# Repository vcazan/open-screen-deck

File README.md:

# Open Screen Deck

Six Waveshare ScreenKey modules (128×128 IPS + switch in each cap) on an
ESP32-S3 carrier you have fabricated, in a case you print. This repo is
the KiCad, Gerbers, OpenSCAD, STLs, firmware, and an optional desktop
companion.

[Build notes](https://vcazan.github.io/open-screen-deck/) ·
[Latest release](https://github.com/vcazan/open-screen-deck/releases/latest)
(macOS/Windows app + firmware `.bin`) ·
[Discord](https://discord.gg/PVCzBBeGQX)

## Build one

1. **Order** — 6× [Waveshare 34168](https://www.waveshare.com/0.85inch-screenkey.htm?sku=34168)
   (about $66, longest lead time). Upload
   [`hardware/pcb/data_streamdeck_gerbers.zip`](hardware/pcb/data_streamdeck_gerbers.zip)
   to [JLCPCB](https://jlcpcb.com) (about $15 for five boards). Full list:
   [`hardware/bom_assembly.csv`](hardware/bom_assembly.csv)
2. **Print** while those ship — four STLs in [`hardware/enclosure/stl/`](hardware/enclosure/stl/),
   PETG or PLA+, no supports:
   `deck_bottom_v14.stl`, `deck_top_v14.stl`, `corner_spacers_x4_v14.stl`,
   optional `deck_stand_v14.stl`
3. **Assemble** — [guide](https://vcazan.github.io/open-screen-deck/build/assembly/),
   about 45 minutes
4. **Flash** over USB-C — [companion](https://github.com/vcazan/open-screen-deck/releases/latest)
   (Settings → Firmware) or Arduino /
   [esptool](https://vcazan.github.io/open-screen-deck/firmware/flashing/).
   Same release has `firmware-0.14.5.bin` plus bootloader and partitions.

Parts land around **$100**. The six modules are most of that. v14 STLs
match the **Rev E** board (59.5 × 108.5 mm); don’t mix with older v13 prints.

| | |
|--|--|
| **Keys** | 6× Waveshare 0.85″ ScreenKey (SKU 34168) |
| **Board** | ESP32-S3-WROOM-1-N16R8 on a **59.5 × 108.5 mm** Rev E carrier |
| **On board** | IMU, VEML7700 ALS, DRV2605L haptics, piezo, 8× SK6812, Qwiic |
| **Displays** | Dual SPI (J1–J3 + SD / J4–J6), 40 MHz + DMA |
| **Case** | 64.9 × 113.9 × 28.2 mm printed deck + optional 25° stand |
| **Firmware** | 0.14.5 (protocol 14) — HID keyboard F13–F24 by default |

Pinout lives in [`hardware/pinout.py`](hardware/pinout.py). Generators
refuse to run if `firmware/config.h` disagrees.

## Firmware

Sources in [`firmware/`](firmware/). Out of the box it types F13–F24.
Pages, labels, icons, microSD animations, auto-dim, glow LEDs, and haptics
are configured over USB serial
([protocol](https://vcazan.github.io/open-screen-deck/firmware/protocol/)).

Prebuilt images are on
[Releases](https://github.com/vcazan/open-screen-deck/releases/latest)
(`firmware-0.14.5.bin`, `.bootloader.bin`, `.partitions.bin`). The companion
bundles the same files. To compile locally:

```bash
./scripts/build_firmware.sh          # also copies bins into the app
./scripts/build_firmware.sh --flash  # then upload to a connected deck
```

Arduino: ESP32S3 Dev Module, USB CDC On Boot enabled, USB-OTG, OPI PSRAM,
16 MB flash (`app3M_fat9M_16MB`). Libraries: Adafruit GFX, ST7735, NeoPixel.

## Companion app

Optional. The deck is a USB keyboard without it. Use the app to draw key
faces, bind host actions, flash firmware, and (on Rev E) drive auto-dim /
glow / self-test.

- **Download:** [Releases](https://github.com/vcazan/open-screen-deck/releases/latest)
  — macOS `.dmg` (unsigned: right-click → Open), Windows `.msi`
- **From source:** `cd app && npm install && npx tauri dev`
- **Plugins:** folders in [`plugins/`](plugins/);
  [directory](https://vcazan.github.io/open-screen-deck/plugins/) ·
  [`plugins/registry.json`](plugins/registry.json)

A push to `main` updates this repo and the docs site. A **GitHub Release**
(installers + firmware bins) is created only when a tag `app-v*` is pushed,
e.g. `app-v0.2.0`.

## Repo map

```
hardware/
  pinout.py          Canonical GPIO + Rev E geometry
  pcb/               KiCad, Gerbers, board BOM
  enclosure/         OpenSCAD v14 + printable STLs
  3d/                Fastener / assembly STEP
firmware/            ESP32-S3 Arduino (0.14.5)
app/                 Tauri companion (Rust + React)
plugins/             Bundled plugins + registry.json
profiles/            Shared layouts (.osdprofile.json)
docs/                MkDocs site
scripts/             PCB / schematic / firmware helpers
```

## Contributing

- **Plugins** — folder in `plugins/` + a registry line
  ([how](https://vcazan.github.io/open-screen-deck/plugins/develop/))
- **Profiles** — export from the app, PR into `profiles/`
- **Hardware** — OpenSCAD is parametric; keep the
  [mechanical contract](docs/mechanical_contract.md) if the PCB should still fit
- **App / firmware** — `cd app && npm test && npm run test:e2e`

## Related projects

Same neighbourhood: [FreeTouchDeck](https://github.com/DustinWatts/FreeTouchDeck)
(one touchscreen), [open-deck](https://github.com/joshr120/open-deck) (one TFT
behind keys), [MacroPad](https://github.com/yuvasaro/MacroPad) (per-key OLED).
This one is six discrete ScreenKey modules on a carrier you can order.

## License

- **Firmware, app, scripts, docs:** [MIT](LICENSE)
- **Hardware (PCB + enclosure):** [CERN-OHL-P v2](hardware/LICENSE)

ScreenKey modules are a [Waveshare](https://www.waveshare.com) product; this
project is not affiliated with or endorsed by Waveshare or Elgato.

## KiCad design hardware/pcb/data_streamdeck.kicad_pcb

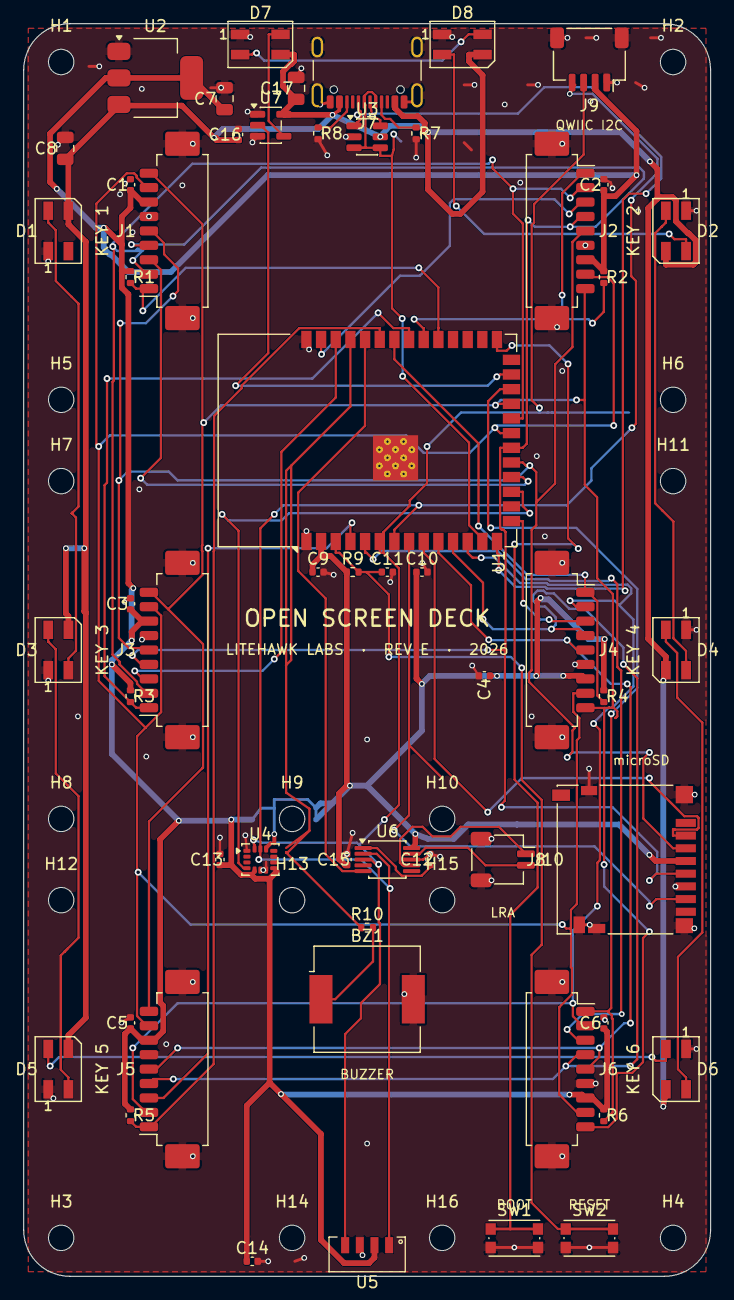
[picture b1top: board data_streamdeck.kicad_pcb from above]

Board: 2 copper layers, 59.5 x 108.5 mm, 71 parts (0 on the bottom side), 49 nets.

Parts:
BZ1: CPT-9019S; Buzzer_CUI_CPT-9019S-SMT
C1, C2, C3, C4, C5, C6, C9, C10, C13, C14, C15, C16: 100nF; C_0402_1005Metric
C7, C8, C17: 10uF; C_0805_2012Metric
C11, C12: 1uF; C_0402_1005Metric
D1, D2, D3, D4, D5, D6, D7, D8: SK6812MINI-E; LED_SK6812MINI_PLCC4_3.5x3.5mm_P1.75mm
H1, H2, H3, H4: M2-corner-case-screw; MountingHole_2.2mm_M2
H5, H6, H7, H8, H9, H10, H11, H12, H13, H14, H15, H16: M2-module-standoff; MountingHole_2.2mm_M2
J1: ScreenKey 1; Molex_PicoBlade_53261-0971_1x09-1MP_P1.25mm_Horizontal
J2: ScreenKey 2; Molex_PicoBlade_53261-0971_1x09-1MP_P1.25mm_Horizontal
J3: ScreenKey 3; Molex_PicoBlade_53261-0971_1x09-1MP_P1.25mm_Horizontal
J4: ScreenKey 4; Molex_PicoBlade_53261-0971_1x09-1MP_P1.25mm_Horizontal
J5: ScreenKey 5; Molex_PicoBlade_53261-0971_1x09-1MP_P1.25mm_Horizontal
J6: ScreenKey 6; Molex_PicoBlade_53261-0971_1x09-1MP_P1.25mm_Horizontal
J7: USB4105-GF-A; USB_C_Receptacle_GCT_USB4105-xx-A_16P_TopMnt_Horizontal
J8: microSD; microSD_HC_Hirose_DM3D-SF
J9: Qwiic; JST_SH_SM04B-SRSS-TB_1x04-1MP_P1.00mm_Horizontal
J10: LRA motor; JST_SH_SM02B-SRSS-TB_1x02-1MP_P1.00mm_Horizontal
R1, R2, R3, R4, R5, R6, R9: 10k; R_0402_1005Metric
R7, R8: 5.1k; R_0402_1005Metric
R10: 100R; R_0402_1005Metric
SW1: BOOT; SW_Push_1P1T_NO_CK_KMR2
SW2: RESET; SW_Push_1P1T_NO_CK_KMR2
U1: ESP32-S3-WROOM-1-N16R8; ESP32-S3-WROOM-1
U2: AMS1117-3.3; SOT-223-3_TabPin2
U3: USBLC6-2SC6; SOT-23-6
U4: LSM6DS3TR-C; LGA-14_3x2.5mm_P0.5mm_LayoutBorder3x4y
U5: VEML7700; VEML7700-TT
U6: DRV2605L; MSOP-10_3x3mm_P0.5mm
U7: 74AHCT1G125; SOT-23-5

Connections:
+3V3: C1.1, C2.1, C3.1, C4.1, C5.1, C6.1, C7.1, C9.1, C10.1, C13.1, C14.1, C15.1, J1.7, J2.7, J3.7, J4.7, J5.7, J6.7, J8.4, J9.2, R1.1, R2.1, R3.1, R4.1, R5.1, R6.1, R9.1, U1.2, U2.2, U4.5, U4.8, U4.12, U5.2, U6.10
BL: J1.8, J2.8, J3.8, J4.8, J5.8, J6.8, U1.21
BOOT: SW1.1, U1.27
CC1: J7.A5, R7.1
CC2: J7.B5, R8.1
CS1: J1.3, U1.18
CS2: J2.3, U1.39
CS3: J3.3, U1.38
CS4: J4.3, U1.15
CS5: J5.3, U1.4
CS6: J6.3, U1.5
DC_A: J1.2, J2.2, J3.2, U1.22
DC_B: J4.2, J5.2, J6.2, U1.12
DRV_REG: C12.1, U6.1
EN: C11.1, R9.2, SW2.1, U1.3
GND: BZ1.2, C1.2, C2.2, C3.2, C4.2, C5.2, C6.2, C7.2, C8.2, C9.2, C10.2, C11.2, C12.2, C13.2, C14.2, C15.2, C16.2, C17.2, D1.1, D2.1, D3.1, D4.1, D5.1, D6.1, D7.1, D8.1, J1.6, J1.MP, J2.6, J2.MP, J3.6, J3.MP, J4.6, J4.MP, J5.6, J5.MP, J6.6, J6.MP, J7.A1, J7.A12, J7.B1, J7.B12, J7.SH, J8.6, J8.9, J8.SH, J9.1, J9.MP, J10.MP, R7.2, R8.2, SW1.2, SW2.2, U1.1, U1.40, U1.41, U2.1, U3.2, U4.1, U4.6, U4.7, U5.3, U6.8, U7.1, U7.3
HAPTIC_EN: U1.36, U6.5
HAP_N: J10.2, U6.9
HAP_P: J10.1, U6.7
IMU_INT: U1.17, U4.4
KEY1: J1.1, R1.2, U1.31
KEY2: J2.1, R2.2, U1.32
KEY3: J3.1, R3.2, U1.33
KEY4: J4.1, R4.2, U1.34
KEY5: J5.1, R5.2, U1.35
KEY6: J6.1, R6.2, U1.24
LED_CH1: D7.2, D8.4
LED_CH2: D2.4, D8.2
LED_CH3: D2.2, D4.4
LED_CH4: D4.2, D6.4
LED_CH5: D5.4, D6.2
LED_CH6: D3.4, D5.2
LED_CH7: D1.4, D3.2
LED_DATA_3V3: U1.25, U7.2
LED_DATA_5V: D7.4, U7.4
MISO: J8.7, U1.8
MOSI_A: J1.5, J2.5, J3.5, J8.3, U1.19
MOSI_B: J4.5, J5.5, J6.5, U1.10
PIEZO: R10.1, U1.37
PIEZO_BZ: BZ1.1, R10.2
RST: J1.9, J2.9, J3.9, J4.9, J5.9, J6.9, U1.23
SCK_A: J1.4, J2.4, J3.4, J8.5, U1.20
SCK_B: J4.4, J5.4, J6.4, U1.11
SCL: J9.4, U1.7, U4.13, U5.1, U6.2
SDA: J9.3, U1.6, U4.14, U5.4, U6.3
SD_CS: J8.2, U1.9
USB_D+: J7.A6, J7.B6, U1.14, U3.1, U3.6
USB_D-: J7.A7, J7.B7, U1.13, U3.3, U3.4
VBUS: C8.1, C16.1, C17.1, D1.3, D2.3, D3.3, D4.3, D5.3, D6.3, D7.3, D8.3, J7.A4, J7.A9, J7.B4, J7.B9, U2.3, U3.5, U7.5

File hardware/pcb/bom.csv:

Reference,Value,Footprint,Qty,MPN,Supplier,Notes
H1-H4,MountingHole 2.2mm,MountingHole:MountingHole_2.2mm_M2,4,,,M2x25 corner case screws pass through into the corner-module nuts
H5-H16,MountingHole 2.2mm,MountingHole:MountingHole_2.2mm_M2,12,,,Module standoff clearance holes (M2x5 into ScreenKey factory standoffs)
J1-J6,Molex PicoBlade 9P right-angle,Connector_Molex:Molex_PicoBlade_53261-0971_1x09-1MP_P1.25mm_Horizontal,6,53261-0971,Molex,Same MX1.25/PicoBlade family as the module connector; in-box cable plugs in; pin1=KEY. Verified alternate: HDGC HDGC1251WR-S-9P (SMT PicoBlade clone; JLC-stocked)
J7,USB-C receptacle,Connector_USB:USB_C_Receptacle_GCT_USB4105-xx-A_16P_TopMnt_Horizontal,1,USB4105-GF-A,GCT,Horizontal top-mount; port exits rear board edge @ X=29.75mm
J8,microSD push-push,Connector_Card:microSD_HC_Hirose_DM3D-SF,1,DM3D-SF,Hirose,Card ejects right board edge; SPI mode on bus A
J9,Qwiic / StemmaQT 4P,Connector_JST:JST_SH_SM04B-SRSS-TB_1x04-1MP_P1.00mm_Horizontal,1,SM04B-SRSS-TB,JST,I2C expansion; exits rear wall next to USB
J10,LRA motor 2P,Connector_JST:JST_SH_SM02B-SRSS-TB_1x02-1MP_P1.00mm_Horizontal,1,SM02B-SRSS-TB,JST,Haptic LRA (e.g. Vybronics VG0832013D) plugs in
U1,ESP32-S3-WROOM-1-N16R8,RF_Module:ESP32-S3-WROOM-1,1,ESP32-S3-WROOM-1-N16R8,Espressif,16MB flash 8MB PSRAM native USB; dual SPI display driver
U2,AMS1117-3.3,Package_TO_SOT_SMD:SOT-223-3_TabPin2,1,AMS1117-3.3,AMS,1A 3.3V LDO from USB 5V — headroom for 6 backlights + SD + sensors
U3,USBLC6-2SC6,Package_TO_SOT_SMD:SOT-23-6,1,USBLC6-2SC6,ST,USB ESD protection on D+/D-/VBUS
U4,LSM6DS3TR-C IMU,Package_LGA:LGA-14_3x2.5mm_P0.5mm_LayoutBorder3x4y,1,LSM6DS3TR-C,ST,6-axis accel+gyro; INT1 on IO9 for wake-on-pickup / tap
U5,VEML7700 ambient light,OpenScreenDeck:VEML7700-TT,1,VEML7700-TT,Vishay,I2C ALS for auto backlight dimming; needs light window in enclosure front
U6,DRV2605L haptic driver,Package_SO:MSOP-10_3x3mm_P0.5mm,1,DRV2605LDGSR,TI,LRA driver with effect library; EN on IO44
U7,74AHCT1G125 level shifter,Package_TO_SOT_SMD:SOT-23-5,1,SN74AHCT1G125DBVR,TI,3.3V -> 5V LED data buffer for SK6812 chain
D1-D8,SK6812MINI-E RGB LED,LED_SK6812MINI:LED_SK6812MINI_PLCC4_3.5x3.5mm_P1.75mm,8,SK6812MINI-E,OPSCO,Edge-glow chain: 2 rear + 6 side; 5V VBUS powered; data from U7
BZ1,Piezo buzzer,Buzzer_Beeper:Buzzer_CUI_CPT-9019S-SMT,1,CPT-9019S-SMT-TR,CUI,4kHz passive piezo; LEDC tone on IO43 via R10
SW1,BOOT tactile C&K KMR2,Button_Switch_SMD:SW_Push_1P1T_NO_CK_KMR2,1,KMR221GLFS,C&K,GPIO0 strap — hold for USB download mode
SW2,RESET tactile C&K KMR2,Button_Switch_SMD:SW_Push_1P1T_NO_CK_KMR2,1,KMR221GLFS,C&K,EN to GND — tap while holding BOOT to enter bootloader
C1-C6,100nF 0402,Capacitor_SMD:C_0402_1005Metric,6,,,Per ScreenKey VCC
C7,10uF 0805,Capacitor_SMD:C_0805_2012Metric,1,,,LDO output bulk
C8,10uF 0805,Capacitor_SMD:C_0805_2012Metric,1,,,LDO input
C9-C11,100nF/1uF 0402,Capacitor_SMD:C_0402_1005Metric,3,,,ESP32 decoupling + EN RC
C12,1uF 0402,Capacitor_SMD:C_0402_1005Metric,1,,,DRV2605L VREG
C13-C15,100nF 0402,Capacitor_SMD:C_0402_1005Metric,3,,,IMU / ALS / haptic decoupling
C16,100nF 0402,Capacitor_SMD:C_0402_1005Metric,1,,,Level shifter 5V decoupling
C17,10uF 0805,Capacitor_SMD:C_0805_2012Metric,1,,,LED 5V rail bulk
R1-R6,10k 0402,Resistor_SMD:R_0402_1005Metric,6,,,KEY line pull-ups
R7-R8,5.1k 0402,Resistor_SMD:R_0402_1005Metric,2,,,USB-C CC1/CC2 pulldowns
R9,10k 0402,Resistor_SMD:R_0402_1005Metric,1,,,EN pull-up
R10,100R 0402,Resistor_SMD:R_0402_1005Metric,1,,,Piezo series resistor

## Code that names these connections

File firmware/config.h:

/**
 * config.h — every pin, constant, and tunable in one place.
 *
 * The canonical pinout lives in hardware/pinout.py: the PCB/schematic
 * generators cross-check this file against it at generation time and
 * hard-fail on divergence. If you change a pin here, change pinout.py
 * and regenerate the hardware in the same commit.
 */

#pragma once

#include <Arduino.h>

// ── Identity ────────────────────────────────────────────────────────
#define FIRMWARE_VERSION "0.14.5"
#define PROTOCOL_VERSION 14

// ── Debug ───────────────────────────────────────────────────────────
// 1 → emit {"event":"dbg",...} lines for every draw/blit/batch change so
// the companion console shows exactly which slot hits which display.
#define DEBUG_DRAW 1

// ── Pins (ESP32-S3-WROOM-1 on the Rev E carrier PCB) ────────────────
// SPI bus A (FSPI): panels J1-J3 + microSD
#define PIN_MOSI_A 11
#define PIN_SCK_A  12
#define PIN_MISO   15   // SD read (displays are write-only)
#define PIN_DC_A   14
#define PIN_SD_CS  16   // microSD chip select
// SPI bus B (HSPI): panels J4-J6
#define PIN_MOSI_B 17
#define PIN_SCK_B  18
#define PIN_DC_B   8
// Shared display lines
#define PIN_RST 21      // reset, all panels on both buses
#define PIN_BL  13      // backlight (LEDC PWM — ALS auto-dim)
// I2C: IMU + ambient light + haptic driver + Qwiic port
#define PIN_SDA     6
#define PIN_SCL     7
#define PIN_IMU_INT 9   // LSM6DS3TR-C INT1 (pickup / tap)
// Outputs
#define PIN_LED_DATA  48  // SK6812 chain (via level shifter)
#define PIN_PIEZO     43  // LEDC tone
#define PIN_HAPTIC_EN 44  // DRV2605L enable

// Legacy aliases (pre-Rev E single-bus names)
#define PIN_MOSI PIN_MOSI_A
#define PIN_SCK  PIN_SCK_A
#define PIN_DC   PIN_DC_A

// ── LEDs ────────────────────────────────────────────────────────────
// Logical order: 0-5 = per-key status (J1..J6), 6 = rear-left (link),
// 7 = rear-right (SD). LED_CHAIN[] in leds.cpp maps chain position →
// logical index (physical routing order differs).
#define LED_COUNT 8
#define LED_REAR_LINK 6
#define LED_REAR_SD   7

// Per-module chip selects and key switch inputs, in wiring order J1..J6.
extern const uint8_t CS_PINS[];
extern const uint8_t KEY_PINS[];

// ── Geometry ────────────────────────────────────────────────────────
#define KEY_COUNT 6                          // physical screens/switches
#define MAX_PAGES 8                          // slot storage ceiling
#define TOTAL_KEYS (KEY_COUNT * MAX_PAGES)   // global key slots (48)
#define FRAME_BYTES (128 * 128 * 2)          // one RGB565 key frame

// ── Media ───────────────────────────────────────────────────────────
// Transparency sentinel (big-endian bytes 0x08,0x21): icon pixels with
// this value adopt the key's background color at draw time, so recoloring
// a key never requires re-uploading its image.
#define TRANSPARENT_HI 0x08
#define TRANSPARENT_LO 0x21

// ── Reserved HID codes ──────────────────────────────────────────────
// These sit in the 224–239 gap of the Arduino keymap — clear of F13–F24
// at 240+ and named keys below 0xDA. A key bound to a page code switches
// pages on-device, standalone AND under the companion, so the firmware
// and the app never fight over page state.
// 224..229 are silent sentinels: never typed; they exist so the companion
// can arm multi-tap detection for host-only actions.
#define HID_INTERNAL_MIN 224
#define HID_INTERNAL_MAX 239
#define HID_PAGE_PREV 230
#define HID_PAGE_NEXT 231
#define HID_PAGE_BASE 232   // 232..239 → go to page 0..7

// ── Timing ──────────────────────────────────────────────────────────
#define DEBOUNCE_MS 50
// Multi-tap: max ms between taps of one sequence. Only keys with a double
// or triple binding ever wait — single-only keys fire with zero latency.
#define TAP_WINDOW_MS 300
// Companion heartbeat: no PING for this long → fall back to plain HID.
#define COMPANION_TIMEOUT_MS 6000
